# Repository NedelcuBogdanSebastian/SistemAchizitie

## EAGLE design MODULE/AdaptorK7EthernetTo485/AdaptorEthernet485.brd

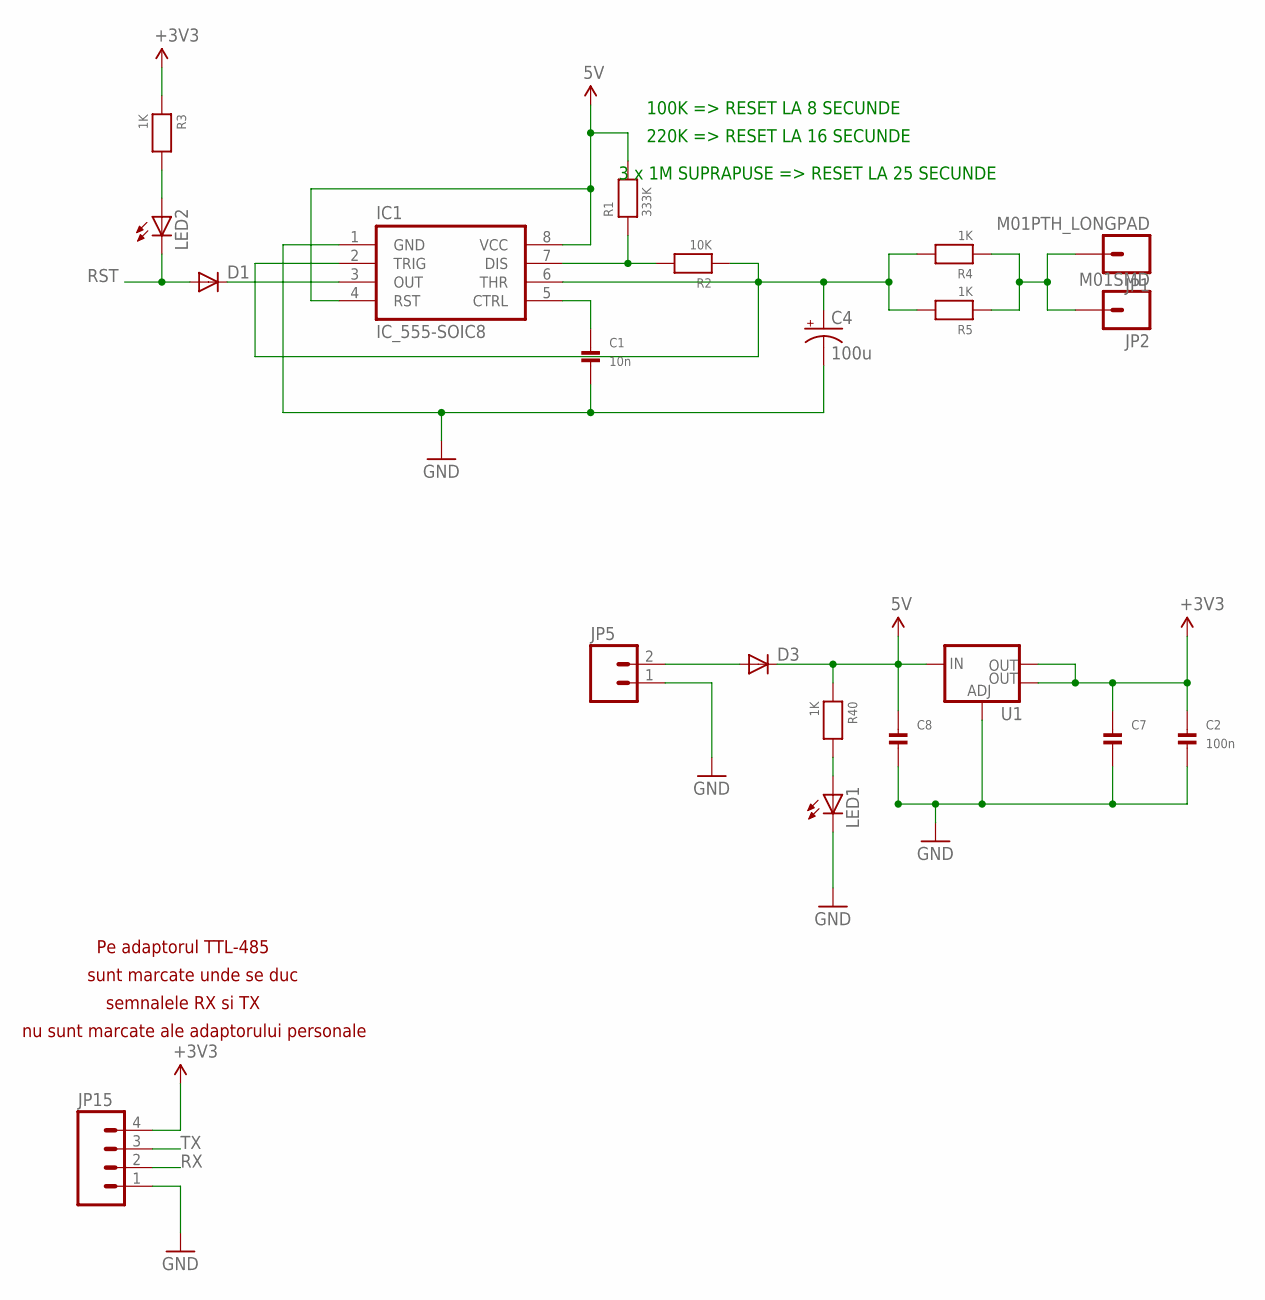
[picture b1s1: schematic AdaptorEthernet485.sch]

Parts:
C1: 10n; _0805MP
C2: 100n; _0805MP
C4: 100u; CPOL-RADIAL-10UF-25V
C7, C8: CAP_CERAMIC1206; 1206
D1, D3: DIODE-DO214AA; DO214AA
IC1: IC_555-SOIC8; SOIC-8
JP1: M01PTH_LONGPAD; 1X01_LONGPAD
JP2: M01SMD; LUXEON-PAD
JP5: M02PTH4; 1X02_XTRA_BIG
JP15: M04LONGPADS; 1X04_LONGPADS
LED1, LED2: LED-3MM-NO_SILK; LED3MM-NS
R1: 333K; _0805MP
R2: 10K; _0805MP
R3, R4, R5, R40: 1K; _0805MP
U1: V_REG_LM1117SOT223; SOT223

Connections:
5V: C8.1, D3.C, IC1.4 (RST), IC1.8 (VCC), R1.2, R40.1, U1.3 (IN)
CTRL: C1.1, IC1.5 (CTRL)
GND: C1.2, C2.2, C4.2 (-), C7.2, C8.2, IC1.1 (GND), JP5.1, JP15.1, LED1.K (C), U1.1 (ADJ)
unnamed: D3.A, JP5.2
unnamed: LED2.A, R3.2
unnamed: C4.1 (+), IC1.2 (TRIG), IC1.6 (THR), R2.1, R4.2, R5.2
unnamed: D1.C, IC1.3 (OUT)
unnamed: IC1.7 (DIS), R1.1, R2.2
unnamed: JP1.1, JP2.P$1, R4.1, R5.1
unnamed: LED1.A, R40.2
RST: D1.A, LED2.K (C)
RX: JP15.2
TX: JP15.3
VCC: C2.1, C7.1, JP15.4, R3.1, U1.2 (OUT), U1.4 (OUT)

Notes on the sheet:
Pe adaptorul TTL-485
sunt marcate unde se duc
semnalele RX si TX
nu sunt marcate ale adaptorului personale
3 x 1M SUPRAPUSE => RESET LA 25 SECUNDE
220K => RESET LA 16 SECUNDE
100K => RESET LA 8 SECUNDE

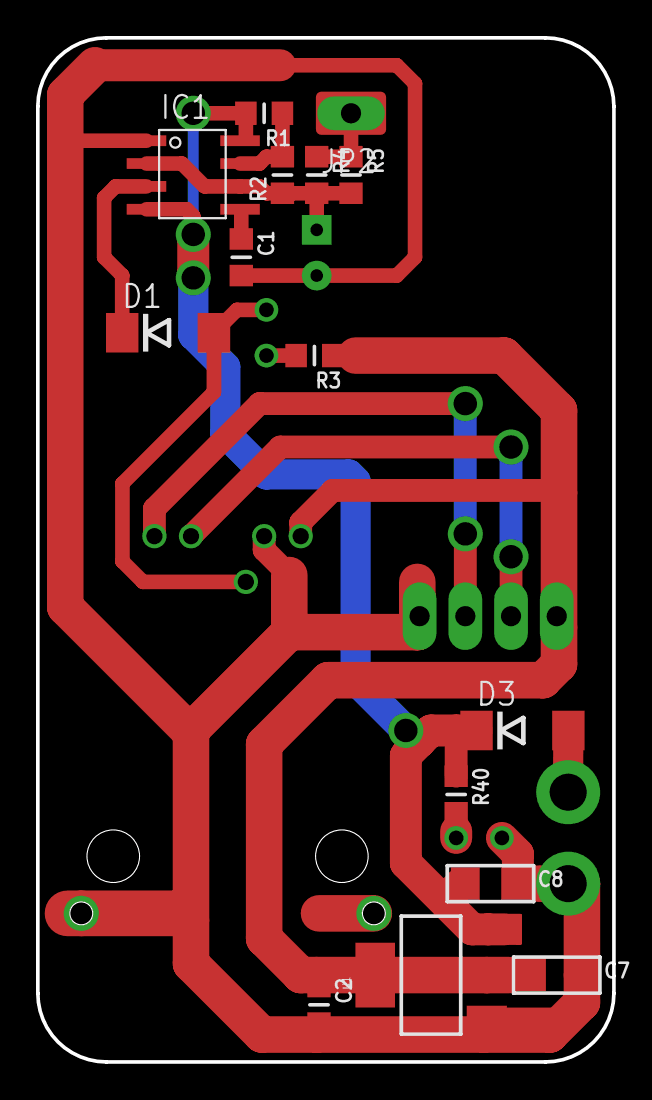
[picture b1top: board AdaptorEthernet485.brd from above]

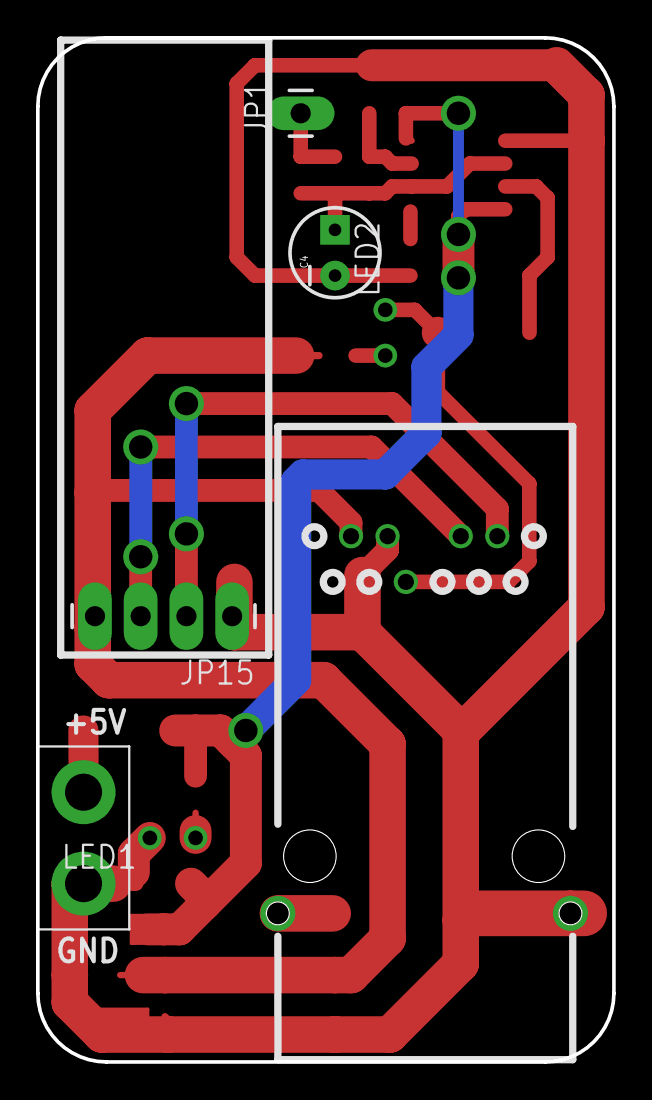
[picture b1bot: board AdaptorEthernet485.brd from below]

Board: 2 copper layers, 32.0 x 56.9 mm, 21 parts (6 on the bottom side), 12 nets.

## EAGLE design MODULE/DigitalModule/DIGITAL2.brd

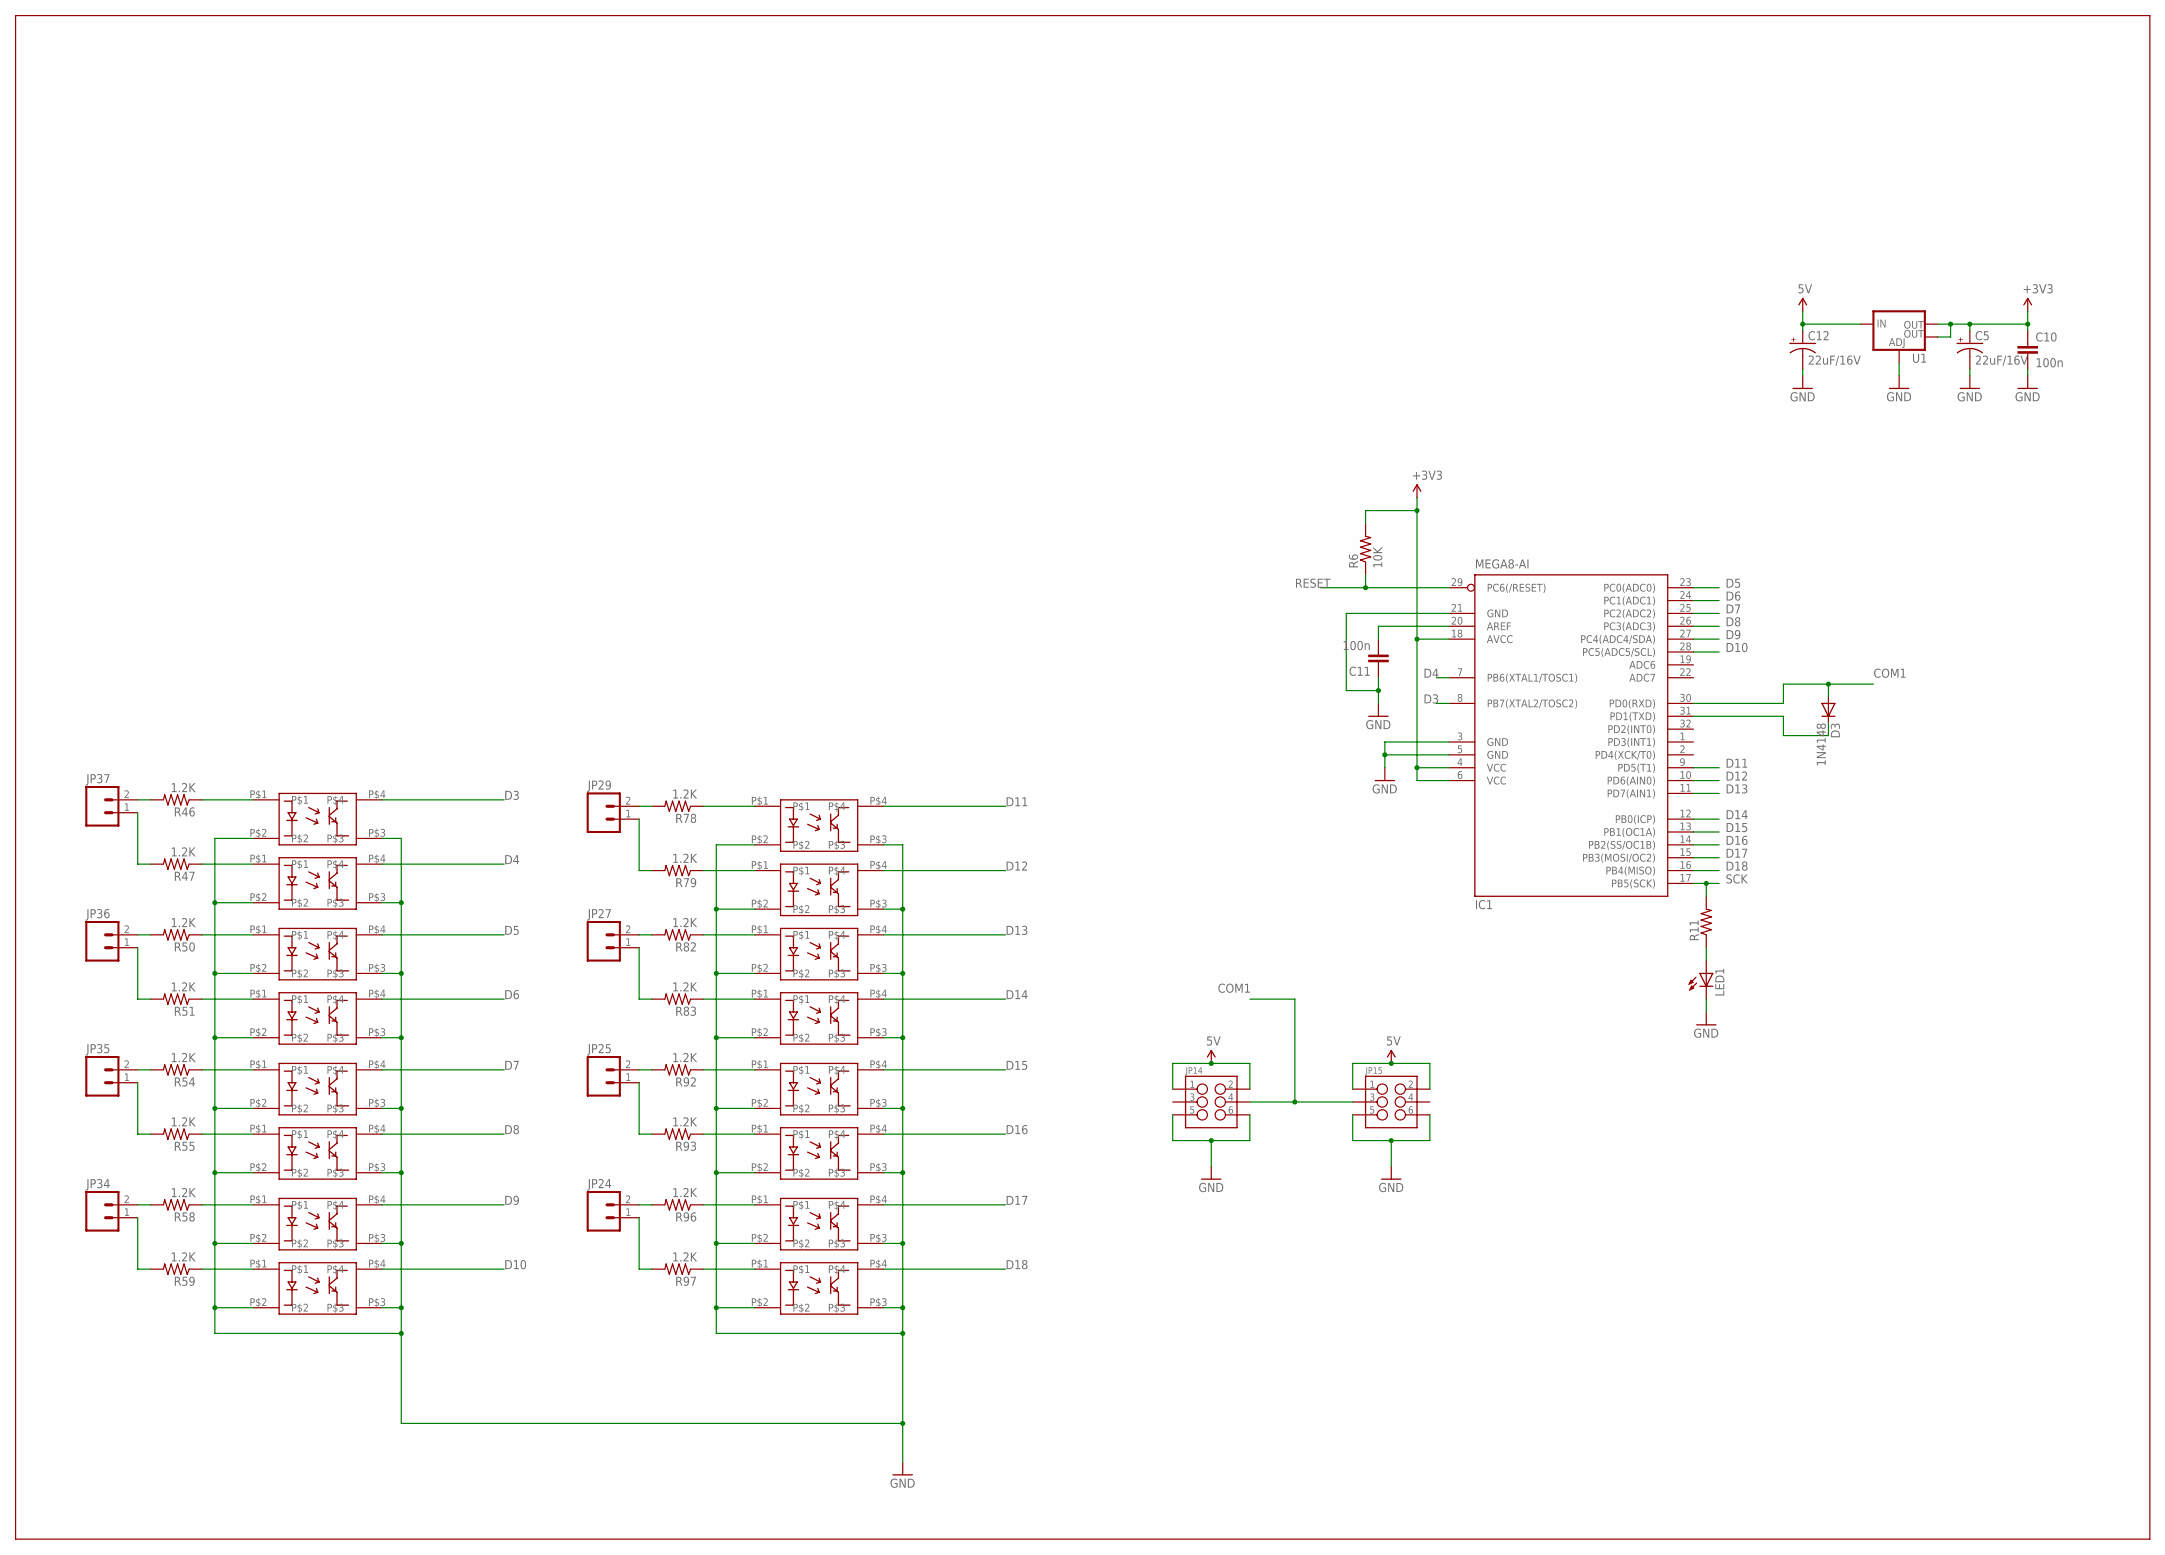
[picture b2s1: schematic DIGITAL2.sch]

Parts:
C5, C12: 22uF/16V; EIA3216
C10, C11: 100n; 0805
D3: 1N4148; MINIMELF
IC1: MEGA8-AI; TQFP32-08
JP14, JP15: M03X22X3_SILK_MALE_PTH; 2X3
JP24, JP25, JP27, JP29, JP34, JP35, JP36, JP37: M025MM; SCREWTERMINAL-5MM-2
LED1: LEDCHIP-LED0805; CHIP-LED0805
R6: 10K; 0805
R11: RESISTOR0805-RES; 0805
R46, R47, R50, R51, R54, R55, R58, R59, R78, R79, R82, R83, R92, R93, R96, R97: 1.2K; 1206
U1: V_REG_LM1117SOT223; SOT223
U$13, U$14, U$15, U$16, U$17, U$18, U$19, U$20, U$29, U$30, U$31, U$32, U$33, U$34, U$35, U$36: IS181D-I; TLP181-I

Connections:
5V: C12.A (+), JP14.1, JP14.2, JP15.1, JP15.2, U1.3 (IN)
COM1: D3.A, IC1.30 (PD0(RXD)), JP14.4, JP15.3
D3: IC1.8 (PB7(XTAL2/TOSC2)), U$13.P$4
D4: IC1.7 (PB6(XTAL1/TOSC1)), U$14.P$4
D5: IC1.23 (PC0(ADC0)), U$15.P$4
D6: IC1.24 (PC1(ADC1)), U$16.P$4
D7: IC1.25 (PC2(ADC2)), U$17.P$4
D8: IC1.26 (PC3(ADC3)), U$18.P$4
D9: IC1.27 (PC4(ADC4/SDA)), U$19.P$4
D10: IC1.28 (PC5(ADC5/SCL)), U$20.P$4
D11: IC1.9 (PD5(T1)), U$29.P$4
D12: IC1.10 (PD6(AIN0)), U$30.P$4
D13: IC1.11 (PD7(AIN1)), U$31.P$4
D14: IC1.12 (PB0(ICP)), U$32.P$4
D15: IC1.13 (PB1(OC1A)), U$33.P$4
D16: IC1.14 (PB2(SS/OC1B)), U$34.P$4
D17: IC1.15 (PB3(MOSI/OC2)), U$35.P$4
D18: IC1.16 (PB4(MISO)), U$36.P$4
GND: C5.C (-), C10.2, C11.1, C12.C (-), IC1.3 (GND), IC1.5 (GND), IC1.21 (GND), JP14.5, JP14.6, JP15.5, JP15.6, LED1.C, U1.1 (ADJ), U$13.P$2, U$13.P$3, U$14.P$2, U$14.P$3, U$15.P$2, U$15.P$3, U$16.P$2, U$16.P$3, U$17.P$2, U$17.P$3, U$18.P$2, U$18.P$3, U$19.P$2, U$19.P$3, U$20.P$2, U$20.P$3, U$29.P$2, U$29.P$3, U$30.P$2, U$30.P$3, U$31.P$2, U$31.P$3, U$32.P$2, U$32.P$3, U$33.P$2, U$33.P$3, U$34.P$2, U$34.P$3, U$35.P$2, U$35.P$3, U$36.P$2, U$36.P$3
unnamed: LED1.A, R11.1
unnamed: D3.C, IC1.31 (PD1(TXD))
unnamed: JP29.2, R78.2
unnamed: C11.2, IC1.20 (AREF)
unnamed: JP27.2, R82.2
unnamed: JP25.2, R92.2
unnamed: JP24.2, R96.2
unnamed: JP27.1, R83.2
unnamed: JP25.1, R93.2
unnamed: JP24.1, R97.2
unnamed: JP37.2, R46.2
unnamed: JP37.1, R47.2
unnamed: R46.1, U$13.P$1
unnamed: R47.1, U$14.P$1
unnamed: JP36.2, R50.2
unnamed: JP36.1, R51.2
unnamed: R50.1, U$15.P$1
unnamed: R51.1, U$16.P$1
unnamed: JP35.2, R54.2
unnamed: JP35.1, R55.2
unnamed: R54.1, U$17.P$1
unnamed: R55.1, U$18.P$1
unnamed: JP34.2, R58.2
unnamed: JP34.1, R59.2
unnamed: R58.1, U$19.P$1
unnamed: R59.1, U$20.P$1
unnamed: JP29.1, R79.2
unnamed: R78.1, U$29.P$1
unnamed: R79.1, U$30.P$1
unnamed: R82.1, U$31.P$1
unnamed: R83.1, U$32.P$1
unnamed: R92.1, U$33.P$1
unnamed: R93.1, U$34.P$1
unnamed: R96.1, U$35.P$1
unnamed: R97.1, U$36.P$1
RESET: IC1.29 (PC6(/RESET)), R6.1
SCK: IC1.17 (PB5(SCK)), R11.2
VCC: C5.A (+), C10.1, IC1.4 (VCC), IC1.6 (VCC), IC1.18 (AVCC), R6.2, U1.2 (OUT), U1.4 (OUT)

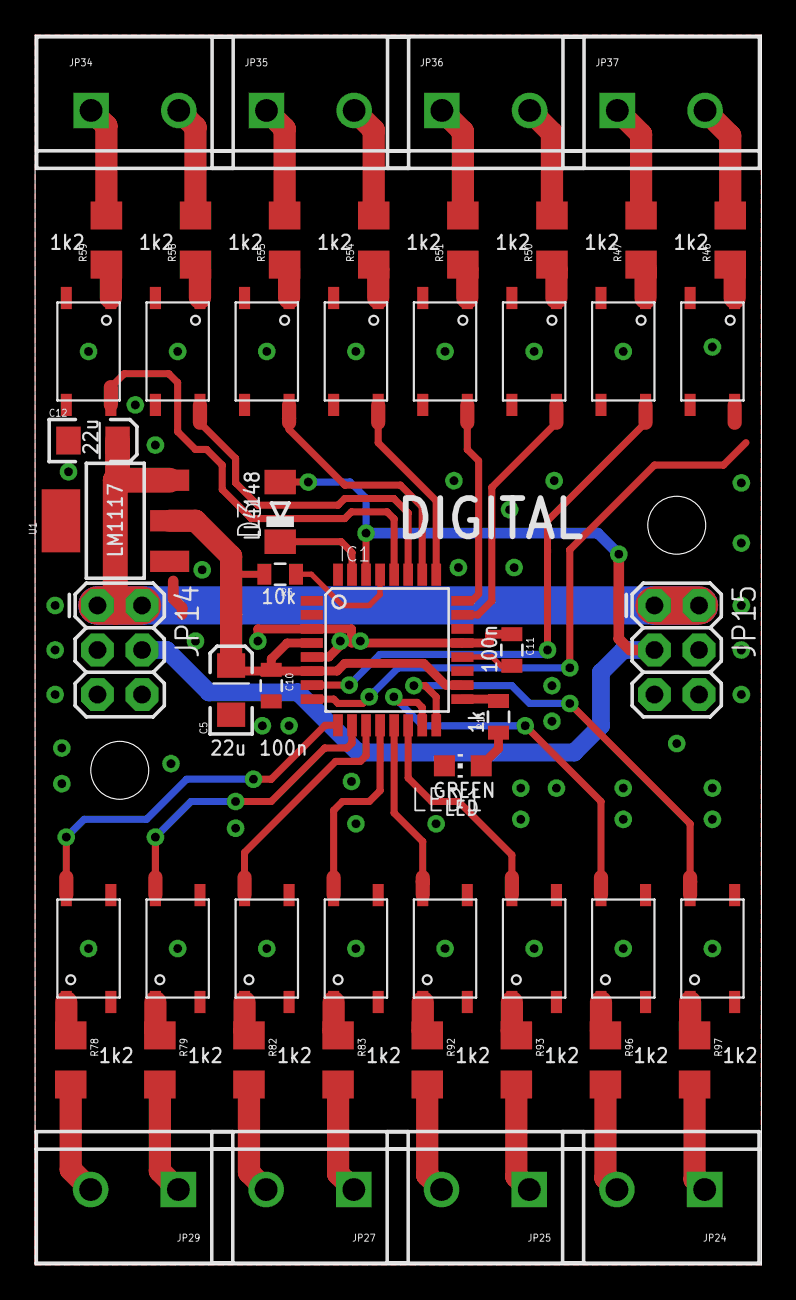
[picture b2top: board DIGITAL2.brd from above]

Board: 2 copper layers, 41.4 x 70.1 mm, 54 parts (0 on the bottom side), 57 nets.

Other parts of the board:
STANDOFF1, STANDOFF3: STAND-OFF

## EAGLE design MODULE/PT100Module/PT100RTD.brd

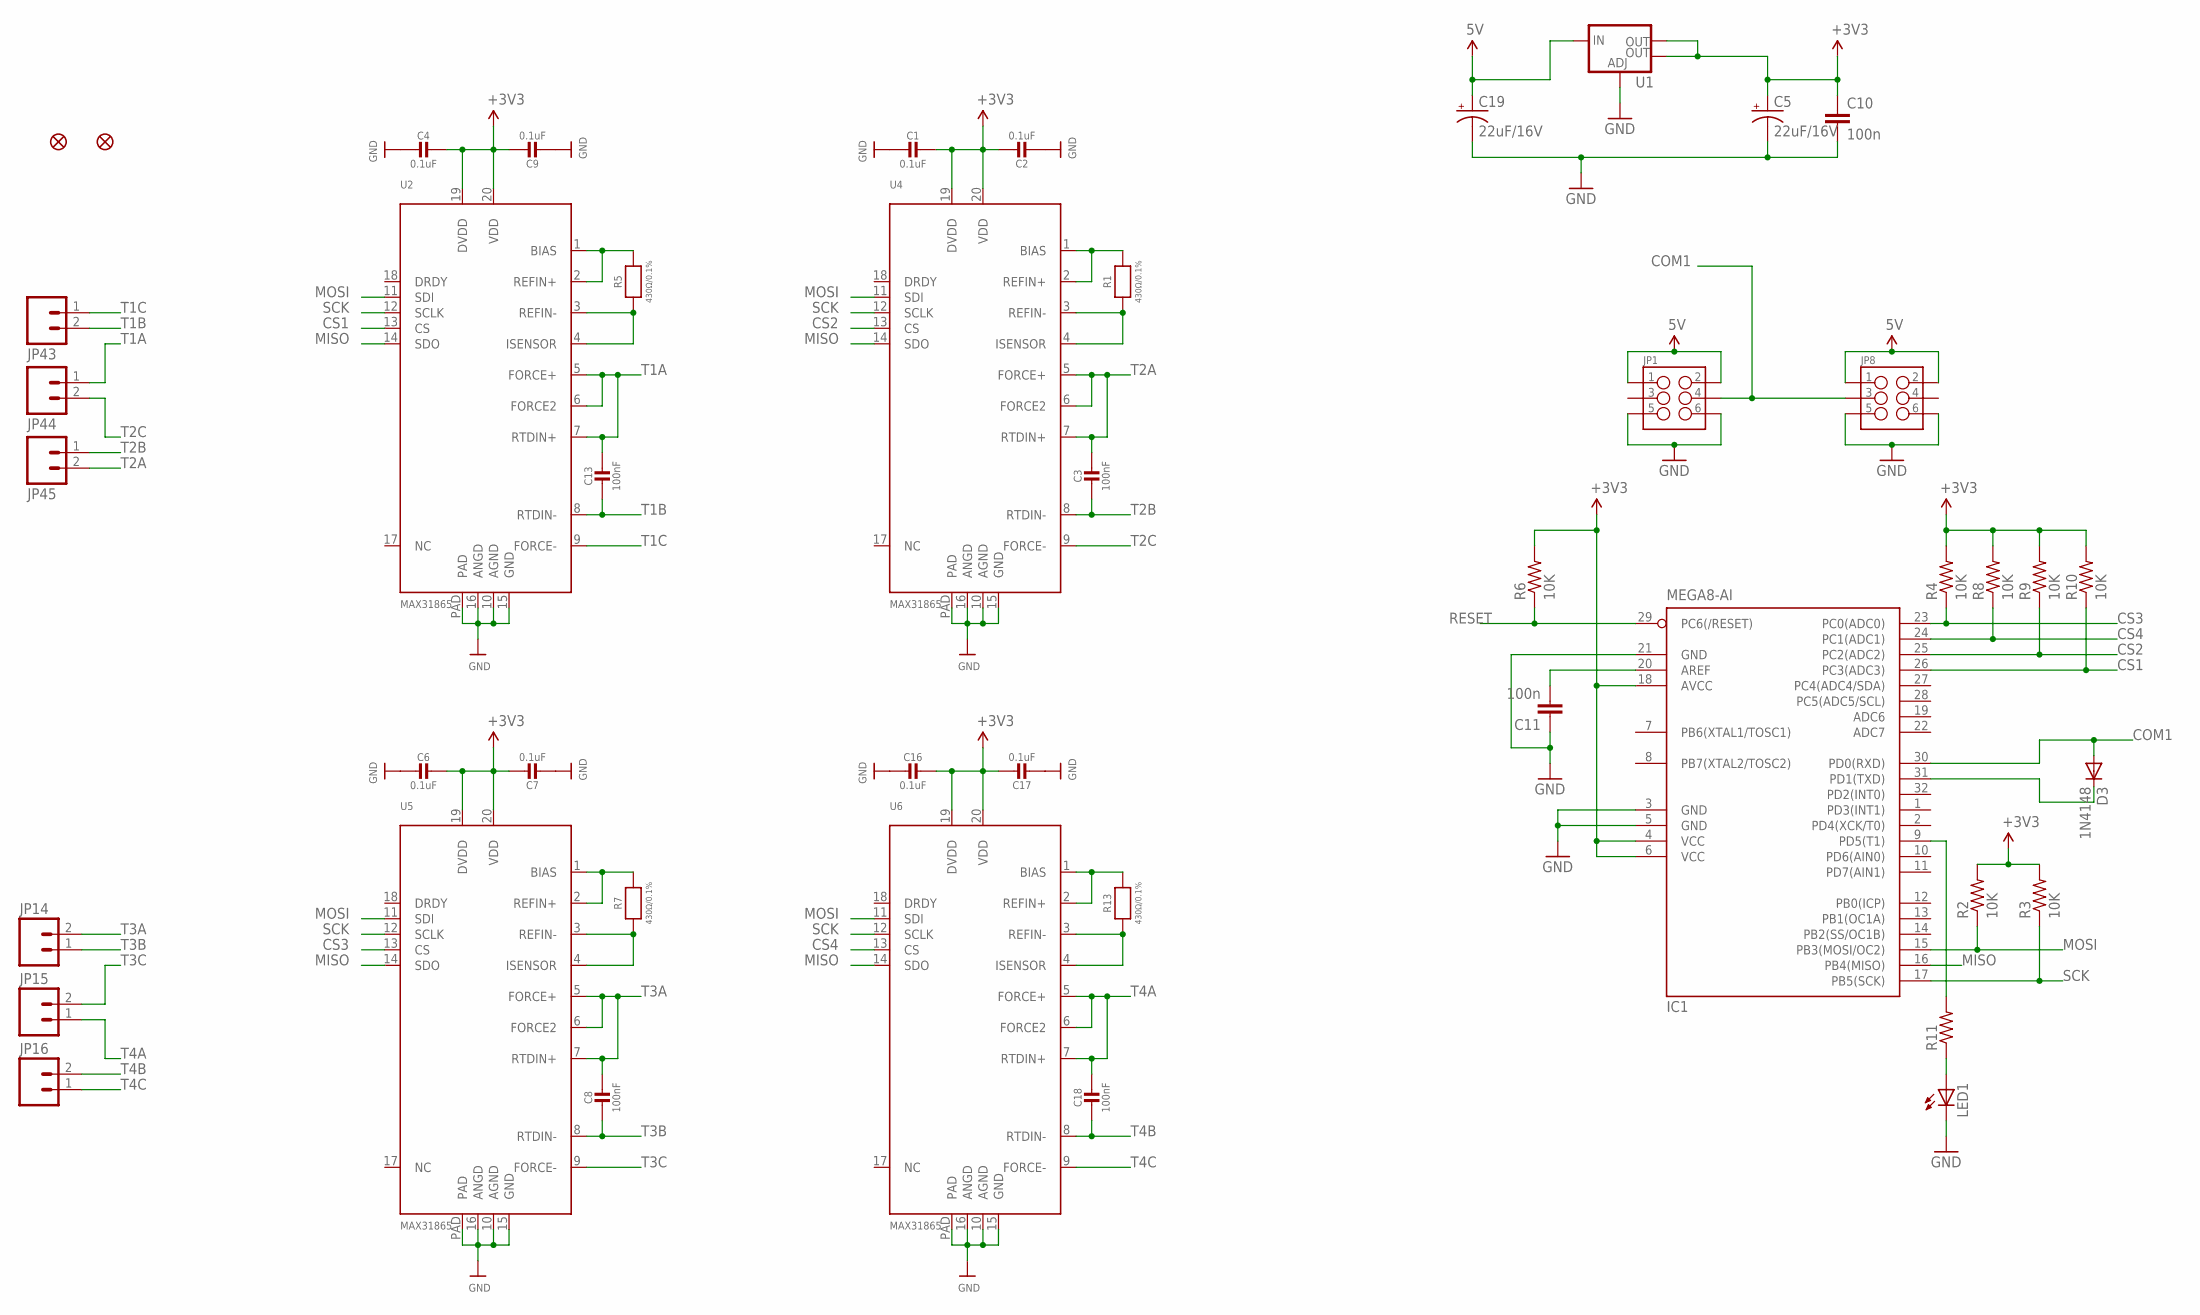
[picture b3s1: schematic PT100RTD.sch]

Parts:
C1, C2, C4, C6, C7, C9, C16, C17: 0.1uF; 0805-NO
C3, C8, C13, C18: 100nF; 0805-NO
C5, C19: 22uF/16V; EIA3216
C10, C11: 100n; 0805
D3: 1N4148; MINIMELF
FD1, FD2: FIDUCIALUFIDUCIAL; FIDUCIAL-MICRO
IC1: MEGA8-AI; TQFP32-08
JP1, JP8: M03X22X3_SILK_MALE_PTH; 2X3
JP14, JP15, JP16, JP43, JP44, JP45: M025MM; SCREWTERMINAL-5MM-2
LED1: LEDCHIP-LED0805; CHIP-LED0805
R1, R5, R7, R13: 430Ω/0.1%; 0805-NO
R2, R3, R4, R6, R8, R9, R10: 10K; 0805
R11: RESISTOR0805-RES; 0805
U1: V_REG_LM1117SOT223; SOT223
U2, U4, U5, U6: MAX31865; QFN20_4MM_0.65MM

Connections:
5V: C19.A (+), JP1.1, JP1.2, JP8.1, JP8.2, U1.3 (IN)
COM1: D3.A, IC1.30 (PD0(RXD)), JP1.4, JP8.3
CS1: IC1.26 (PC3(ADC3)), R10.1, U2.13 (CS)
CS2: IC1.25 (PC2(ADC2)), R9.1, U4.13 (CS)
CS3: IC1.23 (PC0(ADC0)), R4.1, U5.13 (CS)
CS4: IC1.24 (PC1(ADC1)), R8.1, U6.13 (CS)
GND: C1.2, C2.2, C4.2, C5.C (-), C6.2, C7.2, C9.2, C10.2, C11.1, C16.2, C17.2, C19.C (-), IC1.3 (GND), IC1.5 (GND), IC1.21 (GND), JP1.5, JP1.6, JP8.5, JP8.6, LED1.C, U1.1 (ADJ), U2.10 (AGND), U2.15 (GND), U2.16 (ANGD), U2.PAD, U4.10 (AGND), U4.15 (GND), U4.16 (ANGD), U4.PAD, U5.10 (AGND), U5.15 (GND), U5.16 (ANGD), U5.PAD, U6.10 (AGND), U6.15 (GND), U6.16 (ANGD), U6.PAD
MISO: IC1.16 (PB4(MISO)), U2.14 (SDO), U4.14 (SDO), U5.14 (SDO), U6.14 (SDO)
MOSI: IC1.15 (PB3(MOSI/OC2)), R2.1, U2.11 (SDI), U4.11 (SDI), U5.11 (SDI), U6.11 (SDI)
unnamed: LED1.A, R11.1
unnamed: D3.C, IC1.31 (PD1(TXD))
unnamed: R5.2, U2.1 (BIAS), U2.2 (REFIN+)
unnamed: R5.1, U2.3 (REFIN-), U2.4 (ISENSOR)
unnamed: C11.2, IC1.20 (AREF)
unnamed: R1.2, U4.1 (BIAS), U4.2 (REFIN+)
unnamed: R1.1, U4.3 (REFIN-), U4.4 (ISENSOR)
unnamed: R7.2, U5.1 (BIAS), U5.2 (REFIN+)
unnamed: R7.1, U5.3 (REFIN-), U5.4 (ISENSOR)
unnamed: IC1.9 (PD5(T1)), R11.2
unnamed: R13.2, U6.1 (BIAS), U6.2 (REFIN+)
unnamed: R13.1, U6.3 (REFIN-), U6.4 (ISENSOR)
RESET: IC1.29 (PC6(/RESET)), R6.1
SCK: IC1.17 (PB5(SCK)), R3.1, U2.12 (SCLK), U4.12 (SCLK), U5.12 (SCLK), U6.12 (SCLK)
T1A: C13.1, JP44.1, U2.5 (FORCE+), U2.6 (FORCE2), U2.7 (RTDIN+)
T1B: C13.2, JP43.2, U2.8 (RTDIN-)
T1C: JP43.1, U2.9 (FORCE-)
T2A: C3.1, JP45.2, U4.5 (FORCE+), U4.6 (FORCE2), U4.7 (RTDIN+)
T2B: C3.2, JP45.1, U4.8 (RTDIN-)
T2C: JP44.2, U4.9 (FORCE-)
T3A: C8.1, JP14.2, U5.5 (FORCE+), U5.6 (FORCE2), U5.7 (RTDIN+)
T3B: C8.2, JP14.1, U5.8 (RTDIN-)
T3C: JP15.2, U5.9 (FORCE-)
T4A: C18.1, JP15.1, U6.5 (FORCE+), U6.6 (FORCE2), U6.7 (RTDIN+)
T4B: C18.2, JP16.2, U6.8 (RTDIN-)
T4C: JP16.1, U6.9 (FORCE-)
VCC: C1.1, C2.1, C4.1, C5.A (+), C6.1, C7.1, C9.1, C10.1, C16.1, C17.1, IC1.4 (VCC), IC1.6 (VCC), IC1.18 (AVCC), R2.2, R3.2, R4.2, R6.2, R8.2, R9.2, R10.2, U1.2 (OUT), U1.4 (OUT), U2.19 (DVDD), U2.20 (VDD), U4.19 (DVDD), U4.20 (VDD), U5.19 (DVDD), U5.20 (VDD), U6.19 (DVDD), U6.20 (VDD)

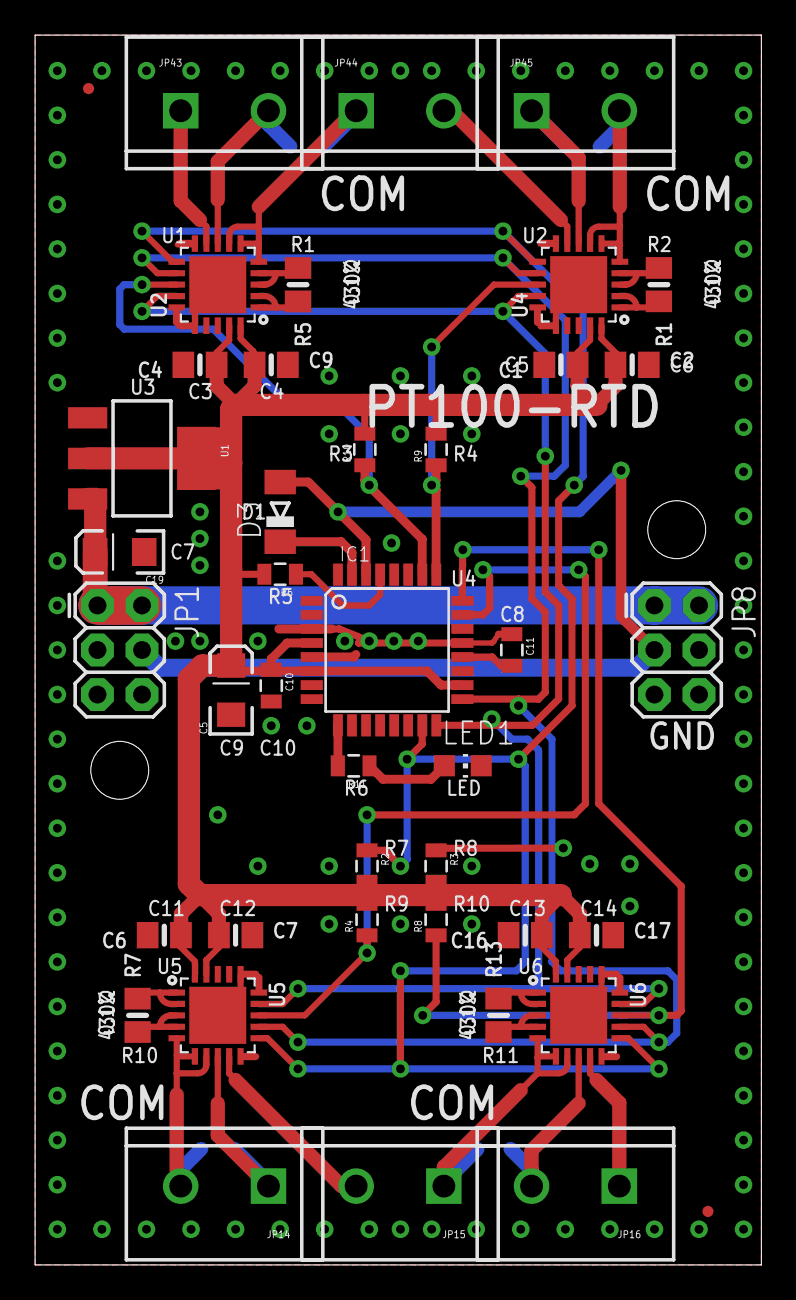
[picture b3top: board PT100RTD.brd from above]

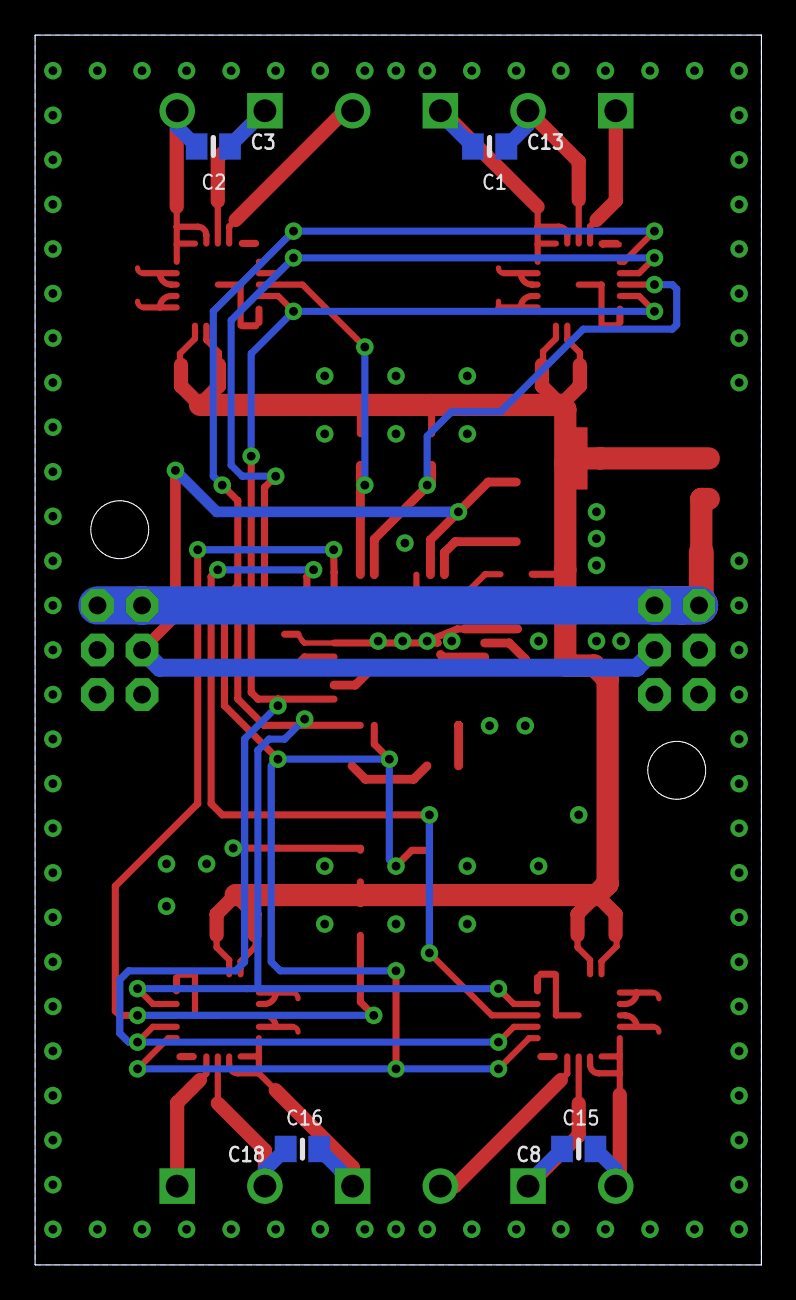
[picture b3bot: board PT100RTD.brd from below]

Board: 2 copper layers, 41.4 x 70.1 mm, 48 parts (4 on the bottom side), 36 nets.

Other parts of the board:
STANDOFF2, STANDOFF3: STAND-OFF

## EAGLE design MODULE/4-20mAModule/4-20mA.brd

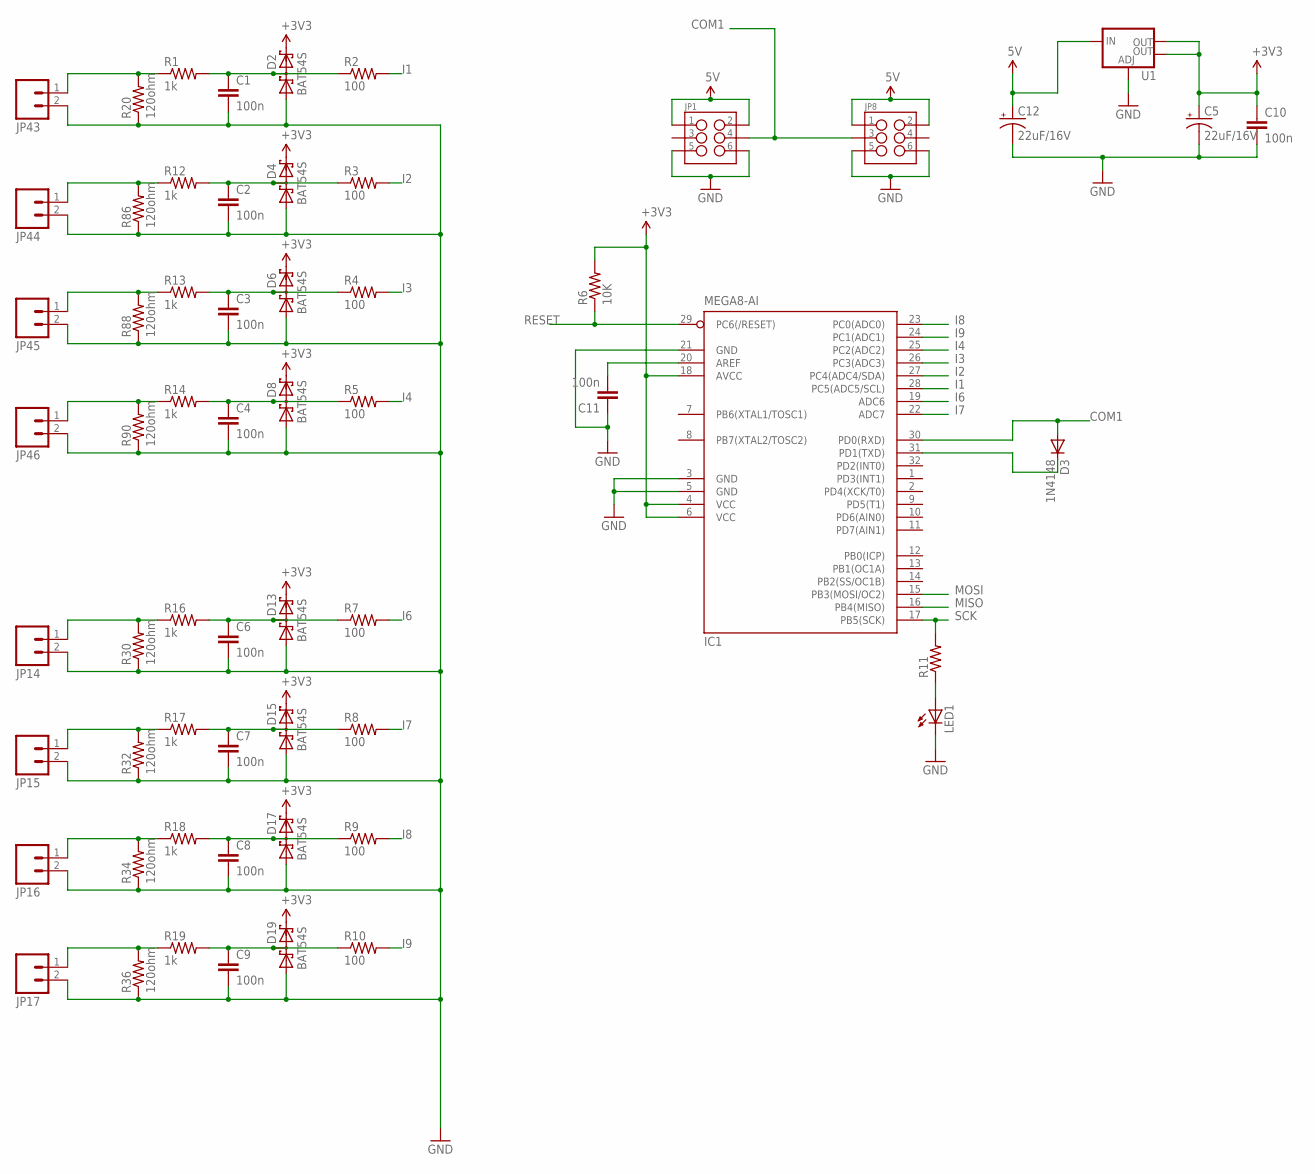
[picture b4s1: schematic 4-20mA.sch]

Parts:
C1, C2, C3, C4, C6, C7, C8, C9, C10, C11: 100n; 0805
C5, C12: 22uF/16V; EIA3216
D2, D4, D6, D8, D13, D15, D17, D19: BAT54S; SOT23
D3: 1N4148; MINIMELF
IC1: MEGA8-AI; TQFP32-08
JP1, JP8: M03X22X3_SILK_MALE_PTH; 2X3
JP14, JP15, JP16, JP17, JP43, JP44, JP45, JP46: M025MM; SCREWTERMINAL-5MM-2
LED1: LEDCHIP-LED0805; CHIP-LED0805
R1, R12, R13, R14, R16, R17, R18, R19: 1k; 0805
R2, R3, R4, R5, R7, R8, R9, R10: 100; 0805
R6: 10K; 0805
R11: RESISTOR0805-RES; 0805
R20, R30, R32, R34, R36, R86, R88, R90: 120ohm; R2010
U1: V_REG_LM1117SOT223; SOT223

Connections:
5V: C12.A (+), JP1.1, JP1.2, JP8.1, JP8.2, U1.3 (IN)
COM1: D3.A, IC1.30 (PD0(RXD)), JP1.4, JP8.3
GND: C1.2, C2.2, C3.2, C4.2, C5.C (-), C6.2, C7.2, C8.2, C9.2, C10.2, C11.1, C12.C (-), D2.1 (A1), D4.1 (A1), D6.1 (A1), D8.1 (A1), D13.1 (A1), D15.1 (A1), D17.1 (A1), D19.1 (A1), IC1.3 (GND), IC1.5 (GND), IC1.21 (GND), JP1.5, JP1.6, JP8.5, JP8.6, JP14.2, JP15.2, JP16.2, JP17.2, JP43.2, JP44.2, JP45.2, JP46.2, LED1.C, R20.1, R30.1, R32.1, R34.1, R36.1, R86.1, R88.1, R90.1, U1.1 (ADJ)
I1: IC1.28 (PC5(ADC5/SCL)), R2.2
I2: IC1.27 (PC4(ADC4/SDA)), R3.2
I3: IC1.26 (PC3(ADC3)), R4.2
I4: IC1.25 (PC2(ADC2)), R5.2
I6: IC1.19 (ADC6), R7.2
I7: IC1.22 (ADC7), R8.2
I8: IC1.23 (PC0(ADC0)), R9.2
I9: IC1.24 (PC1(ADC1)), R10.2
MISO: IC1.16 (PB4(MISO))
MOSI: IC1.15 (PB3(MOSI/OC2))
unnamed: LED1.A, R11.1
unnamed: D3.C, IC1.31 (PD1(TXD))
unnamed: C11.2, IC1.20 (AREF)
unnamed: C9.1, D19.3 (C1A2), R10.1, R19.2
unnamed: C8.1, D17.3 (C1A2), R9.1, R18.2
unnamed: C7.1, D15.3 (C1A2), R8.1, R17.2
unnamed: C6.1, D13.3 (C1A2), R7.1, R16.2
unnamed: C4.1, D8.3 (C1A2), R5.1, R14.2
unnamed: C3.1, D6.3 (C1A2), R4.1, R13.2
unnamed: C2.1, D4.3 (C1A2), R3.1, R12.2
unnamed: C1.1, D2.3 (C1A2), R1.2, R2.1
unnamed: JP43.1, R1.1, R20.2
unnamed: JP14.1, R16.1, R30.2
unnamed: JP44.1, R12.1, R86.2
unnamed: JP45.1, R13.1, R88.2
unnamed: JP46.1, R14.1, R90.2
unnamed: JP15.1, R17.1, R32.2
unnamed: JP16.1, R18.1, R34.2
unnamed: JP17.1, R19.1, R36.2
RESET: IC1.29 (PC6(/RESET)), R6.1
SCK: IC1.17 (PB5(SCK)), R11.2
VCC: C5.A (+), C10.1, D2.2 (C2), D4.2 (C2), D6.2 (C2), D8.2 (C2), D13.2 (C2), D15.2 (C2), D17.2 (C2), D19.2 (C2), IC1.4 (VCC), IC1.6 (VCC), IC1.18 (AVCC), R6.2, U1.2 (OUT), U1.4 (OUT)

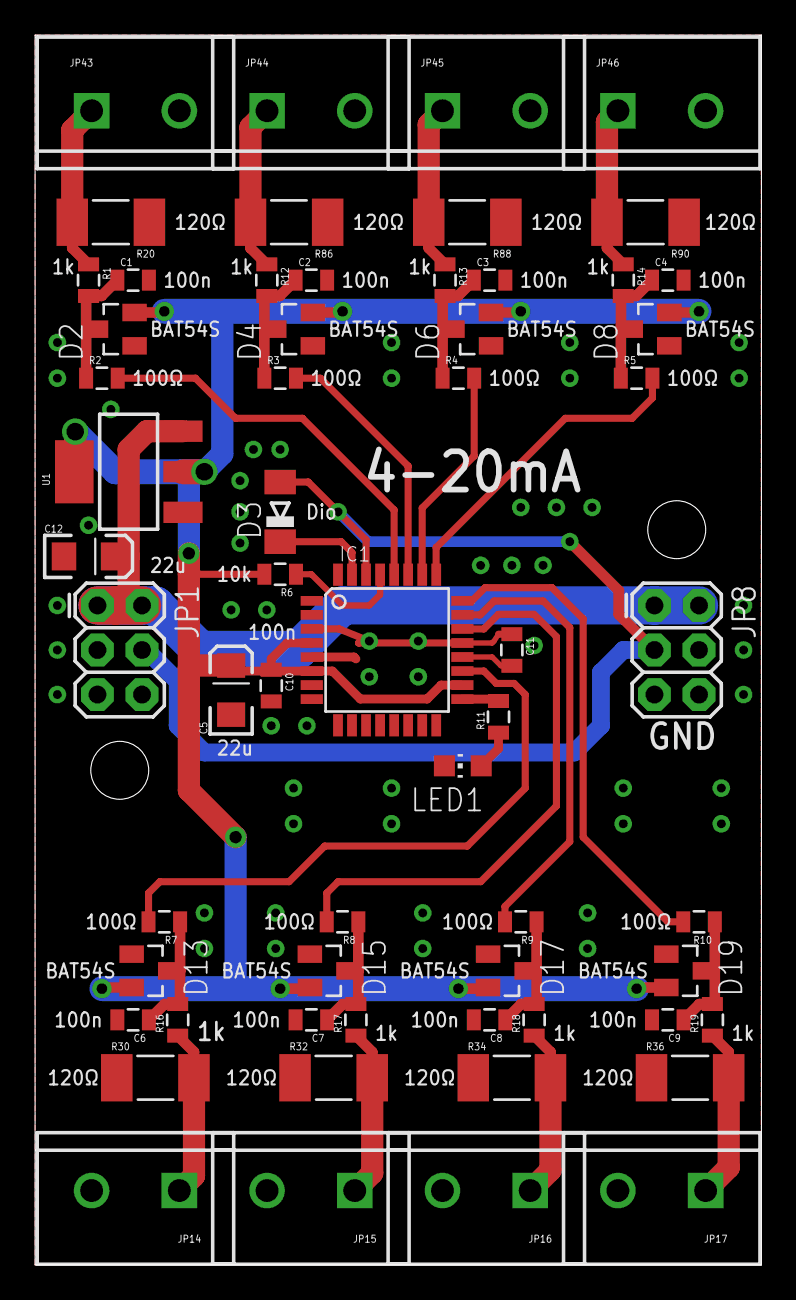
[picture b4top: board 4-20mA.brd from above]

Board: 2 copper layers, 41.4 x 70.1 mm, 62 parts (0 on the bottom side), 33 nets.

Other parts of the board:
STANDOFF2, STANDOFF3: STAND-OFF

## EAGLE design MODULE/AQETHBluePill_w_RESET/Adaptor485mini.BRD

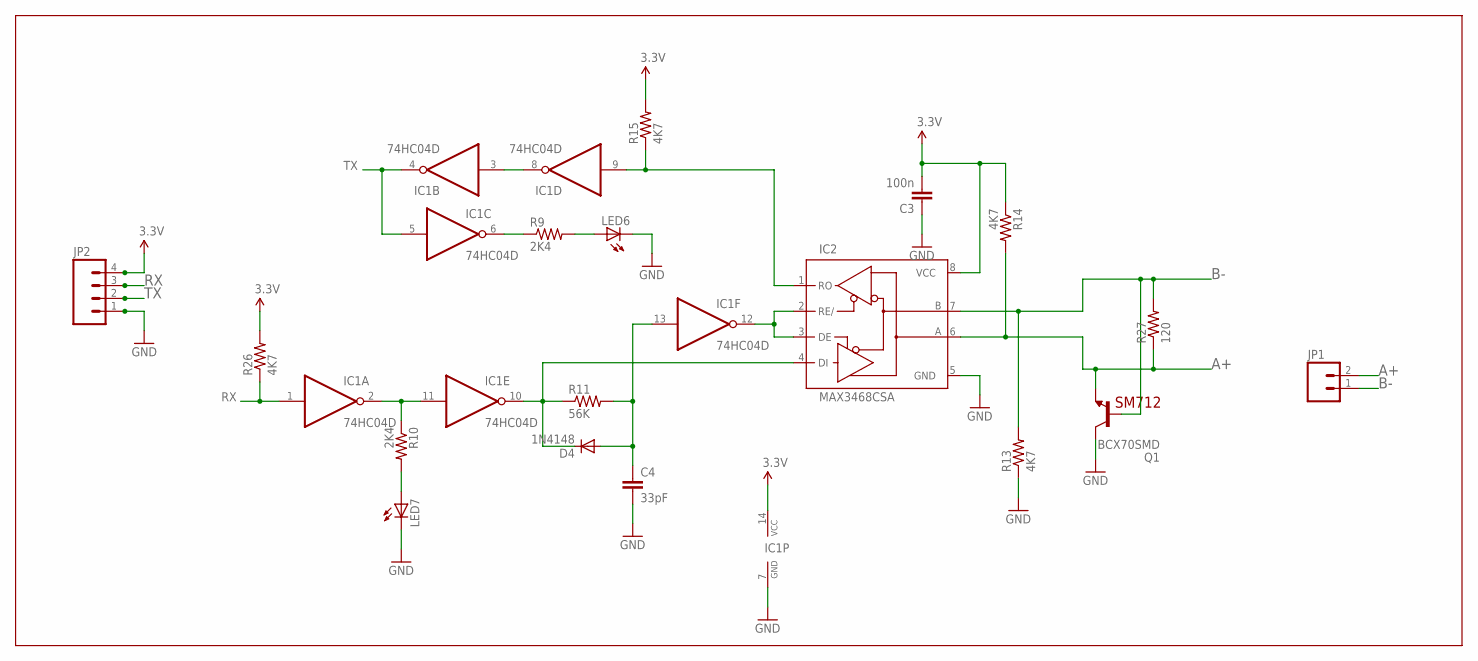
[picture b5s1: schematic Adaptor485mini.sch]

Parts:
C3: 100n; 0805
C4: 33pF; 0805
D4: 1N4148; MINIMELF
IC1: 74HC04D; SO14
IC2: MAX3468CSA; SO08
JP1: M02PTH; 1X02
JP2: M04PTH; 1X04
LED6, LED7: LEDCHIP-LED0805; CHIP-LED0805
Q1: BCX70SMD; SOT23
R9, R10: 2K4; 0805
R11: 56K; 0805
R13, R14, R15, R26: 4K7; 0805
R27: 120; 0805

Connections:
3.3V: C3.2, IC1.14 (VCC), IC2.8 (VCC), JP2.4, R14.1, R15.2, R26.2
A+: IC2.6 (A), JP1.2, Q1.2 (E), R14.2, R27.1
B-: IC2.7 (B), JP1.1, Q1.1 (B), R13.2, R27.2
GND: C3.1, C4.2, IC1.7 (GND), IC2.5 (GND), JP2.1, LED6.C, LED7.C, Q1.3 (C), R13.1
unnamed: LED7.A, R10.2
unnamed: LED6.A, R9.2
unnamed: IC1.2 (O), IC1.11 (I), R10.1
unnamed: IC1.9 (I), IC2.1 (RO), R15.1
unnamed: IC1.3 (I), IC1.8 (O)
unnamed: C4.1, D4.A, IC1.13 (I), R11.2
unnamed: IC1.6 (O), R9.1
unnamed: D4.C, IC1.10 (O), IC2.4 (DI), R11.1
unnamed: IC1.12 (O), IC2.2 (RE/), IC2.3 (DE)
RX: IC1.1 (I), JP2.3, R26.1
TX: IC1.4 (O), IC1.5 (I), JP2.2

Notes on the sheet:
SM712

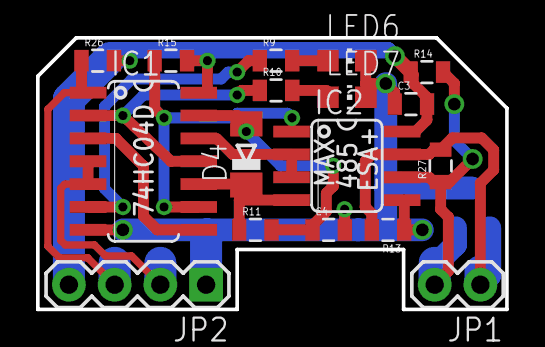
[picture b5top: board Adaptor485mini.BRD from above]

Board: 2 copper layers, 26.1 x 15.1 mm, 18 parts (1 on the bottom side), 15 nets.

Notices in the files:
parts and their libraries:
SparkFun-Connectors: Licensing: CC v3.0 Share-Alike You are welcome to use this library for commercial purposes.
SparkFun-PowerIC: Licensing: Creative Commons ShareAlike 4.0 International - https://creativecommons.org/licenses/by-sa/4.0
